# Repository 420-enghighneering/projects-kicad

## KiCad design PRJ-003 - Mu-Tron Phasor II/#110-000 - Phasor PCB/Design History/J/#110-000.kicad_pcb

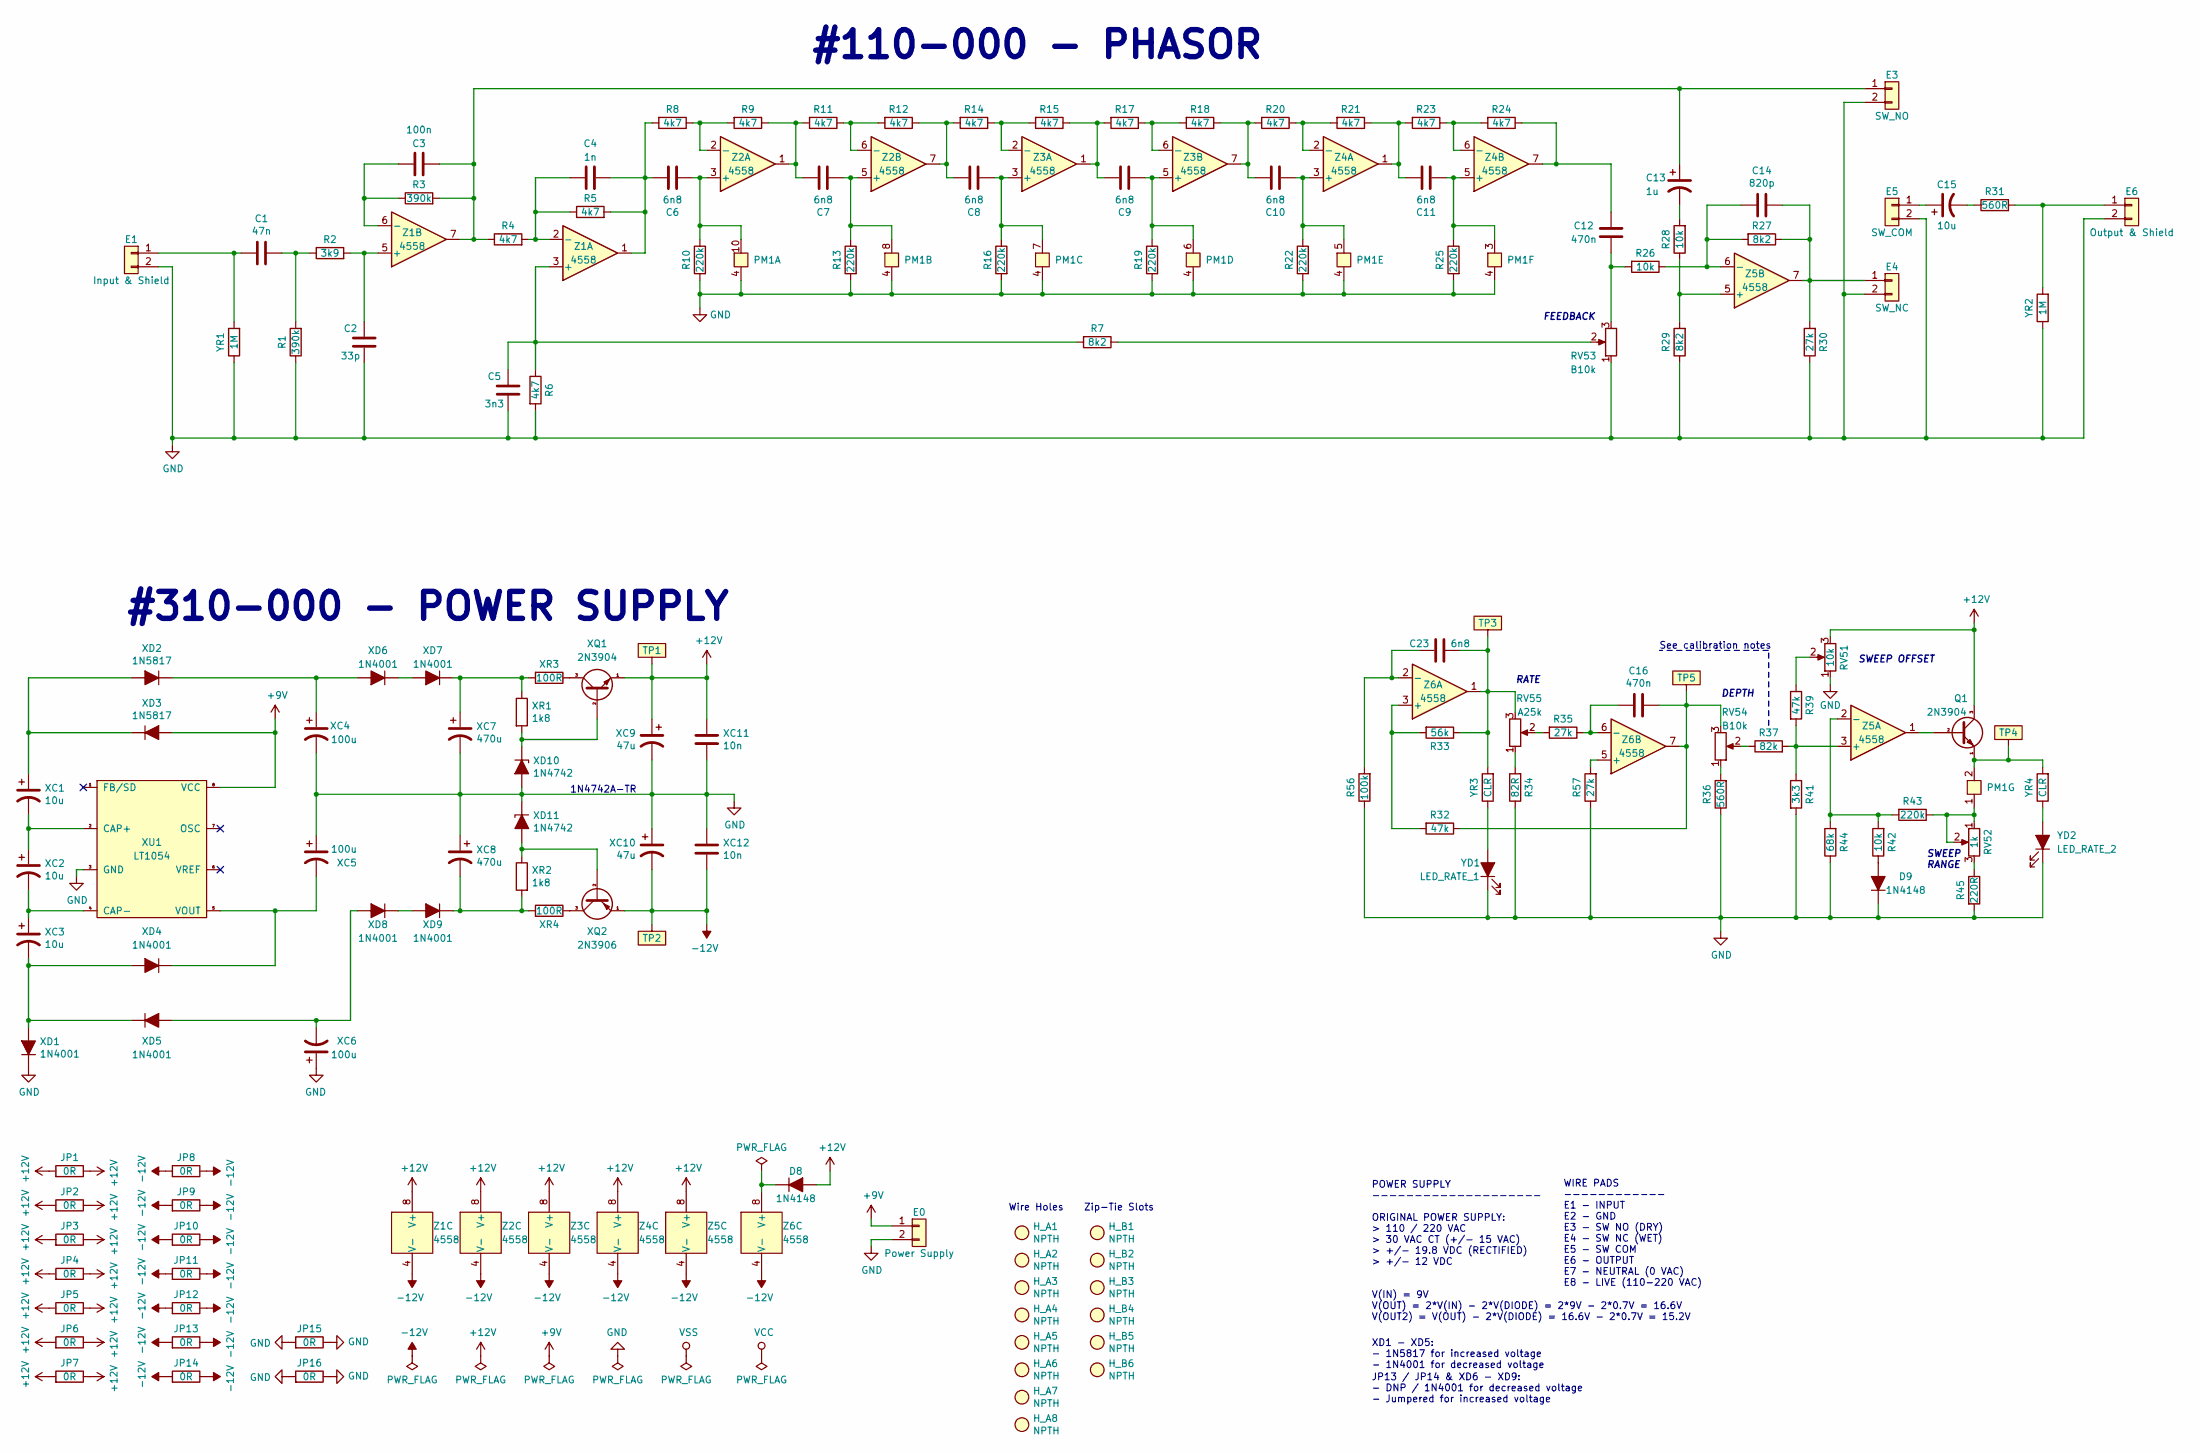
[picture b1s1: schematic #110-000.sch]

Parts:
C1: 47n; C_MKS2F024701C00KSSD
C2: 33p; C_FKP2O100331D00JSSD
C3: 100n; C_MKS2C031001A00KSSD
C4: 1n; C_FKS2G011001A00KSSD
C5: 3n3; C_FKS2G013301A00KSSD
C6, C7, C8, C9, C10, C11, C23: 6n8; C_FKS2G016801B00KSSD
C12, C16: 470n; C_MKS2C034701C00KSSD
C13: 1u; C_UMA1H010MDD
C14: 820p; C_FKP2J008201D00HSSD
C15: 10u; C_UMA1V100MDD
D8, D9: 1N4148; D_P10.16_DO35
E0: Power Supply; E_WIRE_PAD_2x
E1: Input & Shield; E_WIRE_PAD_2x
E3: SW_NO; E_WIRE_PAD_2x
E4: SW_NC; E_WIRE_PAD_2x
E5: SW_COM; E_WIRE_PAD_2x
E6: Output & Shield; E_WIRE_PAD_2x
H_A1, H_A2, H_A3, H_A4, H_A5, H_A6, H_A7, H_A8: NPTH; H_NPTH
H_B1, H_B2, H_B3, H_B4, H_B5, H_B6: NPTH; E_ZIPTIE_NPTH
JP1, JP2, JP3, JP4, JP5, JP6, JP7, JP8, JP9, JP10, JP11, JP12, JP13, JP14, JP15, JP16: 0R; R_0R_JUMPER_P10.16
PM1: Photomodule; PM_DIP-10
Q1: 2N3904; Q_P2.54
R1, R3: 390k; R_P10.16
R2: 3k9; R_P10.16
R4, R5, R6, R8, R9, R11, R12, R14, R15, R17, R18, R20, R21, R23, R24: 4k7; R_P10.16
R7, R27, R29: 8k2; R_P10.16
R10, R13, R16, R19, R22, R25, R43: 220k; R_P10.16
R26, R28, R42: 10k; R_P10.16
R30, R35, R57: 27k; R_P10.16
R31, R36: 560R; R_P10.16
R32, R39: 47k; R_P10.16
R33: 56k; R_P10.16
R34: 82R; R_P10.16
R37: 82k; R_P10.16
R41: 3k3; R_P10.16
R44: 68k; R_P10.16
R45: 220R; R_P10.16
R56: 100k; R_P10.16
RV51: 10k; R_TRIM
RV52: 1k; R_TRIM
RV53, RV54: B10k; R_POT
RV55: A25k; R_POT
TP1: TP1; TP_SMD_R_3mm
TP2: TP2; TP_SMD_R_3mm
TP3: TP3; TP_SMD_R_3mm
TP4: TP4; TP_SMD_R_3mm
TP5: TP5; TP_SMD_R_3mm
XC1, XC2, XC3: 10u; C_UMA1V100MDD
XC4, XC5, XC6: 100u; C_UMA1E101MDD
XC7, XC8: 470u; C_ANGLED
XC9, XC10: 47u; C_UMA1V470MDD
XC11, XC12: 10n; C_FKS2G021001C00KSSD
XD1, XD4, XD5, XD6, XD7, XD8, XD9: 1N4001; D_P10.16
XD2, XD3: 1N5817; D_P10.16
XD10, XD11: 1N4742; D_P10.16_DO35
XQ1: 2N3904; Q_P2.54
XQ2: 2N3906; Q_P2.54
XR1, XR2: 1k8; R_P10.16
XR3, XR4: 100R; R_P10.16
XU1: LT1054; U_DIP-8
YD1: LED_RATE_1; E_WIRE_PAD_2x
YD2: LED_RATE_2; E_WIRE_PAD_2x
YR1, YR2: 1M; R_P10.16
YR3, YR4: CLR; R_P10.16
Z1, Z2, Z3, Z4, Z5, Z6: 4558; U_DIP-8

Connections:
+9V: E0.1, XD3.1 (A), XU1.8 (VCC)
+12V: D8.1 (A), JP1.1, JP1.2, JP2.1, JP2.2, JP3.1, JP3.2, JP4.1, JP4.2, JP5.1, JP5.2, JP6.1, JP6.2, JP7.1, JP7.2, Q1.3 (C), RV51.3, TP1.1, XC9.1, XC11.1, XQ1.1 (E), Z1.8 (V+), Z2.8 (V+), Z3.8 (V+), Z4.8 (V+), Z5.8 (V+)
-12V: JP8.1, JP8.2, JP9.1, JP9.2, JP10.1, JP10.2, JP11.1, JP11.2, JP12.1, JP12.2, JP13.1, JP13.2, JP14.1, JP14.2, TP2.1, XC10.2, XC12.2, XQ2.1 (E), Z1.4 (V-), Z2.4 (V-), Z3.4 (V-), Z4.4 (V-), Z5.4 (V-), Z6.4 (V-)
GND: C2.2, C5.2, D9.2 (K), E0.2, E1.2, E3.2, E4.2, E5.2, E6.2, JP15.1, JP15.2, JP16.1, JP16.2, PM1.4, PM1.9, R1.1, R6.2, R10.2, R13.2, R16.2, R19.2, R22.2, R25.2, R29.1, R30.1, R34.1, R36.1, R41.2, R44.1, R45.2, R56.1, R57.1, RV51.1, RV53.1, XC4.2, XC5.1, XC6.1, XC7.2, XC8.1, XC9.2, XC10.1, XC11.2, XC12.1, XD1.2 (K), XD10.1 (A), XD11.2 (K), XU1.3 (GND), YD1.1 (K), YD2.1 (K), YR1.1, YR2.1
unnamed: C1.1, E1.1, YR1.2
unnamed: C1.2, R1.2, R2.1
unnamed: C2.1, R2.2, Z1.5 (+)
unnamed: C3.1, R3.1, Z1.6 (-)
unnamed: C4.1, R4.2, R5.1, Z1.2 (-)
unnamed: C4.2, C6.1, R5.2, R8.2, Z1.1
unnamed: C5.1, R6.1, R7.2, Z1.3 (+)
unnamed: C6.2, PM1.10, R10.1, Z2.3 (+)
unnamed: C7.1, R9.1, R11.2, Z2.1
unnamed: C7.2, PM1.8, R13.1, Z2.5 (+)
unnamed: C8.1, R12.1, R14.2, Z2.7
unnamed: C8.2, PM1.7, R16.1, Z3.3 (+)
unnamed: C9.1, R15.1, R17.2, Z3.1
unnamed: C9.2, PM1.6, R19.1, Z3.5 (+)
unnamed: C10.1, R18.1, R20.2, Z3.7
unnamed: C10.2, PM1.5, R22.1, Z4.3 (+)
unnamed: C11.1, R21.1, R23.2, Z4.1
unnamed: C11.2, PM1.3, R25.1, Z4.5 (+)
unnamed: C12.1, R24.1, Z4.7
unnamed: C12.2, R26.2, RV53.3
unnamed: C3.2, C13.1, E3.1, R3.2, R4.1, Z1.7
unnamed: C13.2, R28.2
unnamed: C14.1, R26.1, R27.2, Z5.6 (-)
unnamed: C14.2, E4.1, R27.1, R30.2, Z5.7
unnamed: C15.1, E5.1
unnamed: C15.2, R31.1
unnamed: C16.1, R35.1, Z6.6 (-)
unnamed: C16.2, R32.1, RV54.3, TP5.1, Z6.7
unnamed: C23.1, R56.2, Z6.2 (-)
unnamed: C23.2, R33.1, RV55.3, TP3.1, YR3.2, Z6.1
unnamed: D8.2 (K), Z6.8 (V+)
unnamed: D9.1 (A), R42.1
unnamed: E6.1, R31.2, YR2.2
unnamed: PM1.1, R43.1, RV52.1, RV52.2
unnamed: PM1.2, Q1.1 (E), TP4.1, YR4.2
unnamed: Q1.2 (B), Z5.1
unnamed: R7.1, RV53.2
unnamed: R8.1, R9.2, Z2.2 (-)
unnamed: R11.1, R12.2, Z2.6 (-)
unnamed: R14.1, R15.2, Z3.2 (-)
unnamed: R17.1, R18.2, Z3.6 (-)
unnamed: R20.1, R21.2, Z4.2 (-)
unnamed: R23.1, R24.2, Z4.6 (-)
unnamed: R28.1, R29.2, Z5.5 (+)
unnamed: R32.2, R33.2, Z6.3 (+)
unnamed: R34.2, RV55.1
unnamed: R35.2, RV55.2
unnamed: R36.2, RV54.1
unnamed: R37.1, RV54.2
unnamed: R37.2, R39.2, R41.1, Z5.3 (+)
unnamed: R39.1, RV51.2
unnamed: R42.2, R43.2, R44.2, Z5.2 (-)
unnamed: R45.1, RV52.3
unnamed: R57.2, Z6.5 (+)
unnamed: XC1.1, XD2.1 (A), XD3.2 (K)
unnamed: XC1.2, XC2.1, XU1.2 (CAP+)
unnamed: XC2.2, XC3.1, XU1.4 (CAP-)
unnamed: XC3.2, XD1.1 (A), XD4.1 (A), XD5.2 (K)
unnamed: XC4.1, XD2.2 (K), XD6.1 (A)
unnamed: XC5.2, XD4.2 (K), XU1.5 (VOUT)
unnamed: XC6.2, XD5.1 (A), XD8.1 (A)
unnamed: XC7.1, XD7.2 (K), XR1.1, XR3.2
unnamed: XC8.2, XD9.2 (K), XR2.2, XR4.2
unnamed: XD6.2 (K), XD7.1 (A)
unnamed: XD8.2 (K), XD9.1 (A)
unnamed: XD10.2 (K), XQ1.2 (B), XR1.2
unnamed: XD11.1 (A), XQ2.2 (B), XR2.1
unnamed: XQ1.3 (C), XR3.1
unnamed: XQ2.3 (C), XR4.1
unnamed: YD1.2 (A), YR3.1
unnamed: YD2.2 (A), YR4.1

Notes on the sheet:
1N4742A-TR
POWER SUPPLY -------------------- ORIGINAL POWER SUPPLY: > 110 / 220 VAC > 30 VAC CT (+/- 15 VAC) > +/- 19.8 VDC (RECTIFIED) > +/- 12 VDC V(IN) = 9V V(OUT) = 2*V(IN) - 2*V(DIODE) = 2*9V - 2*0.7V = 16.6V V(OUT2) = V(OUT) - 2*V(DIODE) = 16.6V - 2*0.7V = 15.2V
SWEEP OFFSET
SWEEP RANGE
DEPTH
RATE
FEEDBACK
WIRE PADS ------------ E1 - INPUT E2 - GND E3 - SW NO (DRY) E4 - SW NC (WET) E5 - SW COM E6 - OUTPUT E7 - NEUTRAL (0 VAC) E8 - LIVE (110-220 VAC)
XD1 - XD5: - 1N5817 for increased voltage - 1N4001 for decreased voltage
JP13 / JP14 & XD6 - XD9: - DNP / 1N4001 for decreased voltage - Jumpered for increased voltage
#310-000 - POWER SUPPLY
#110-000 - PHASOR
See calibration notes
Zip-Tie Slots
Wire Holes

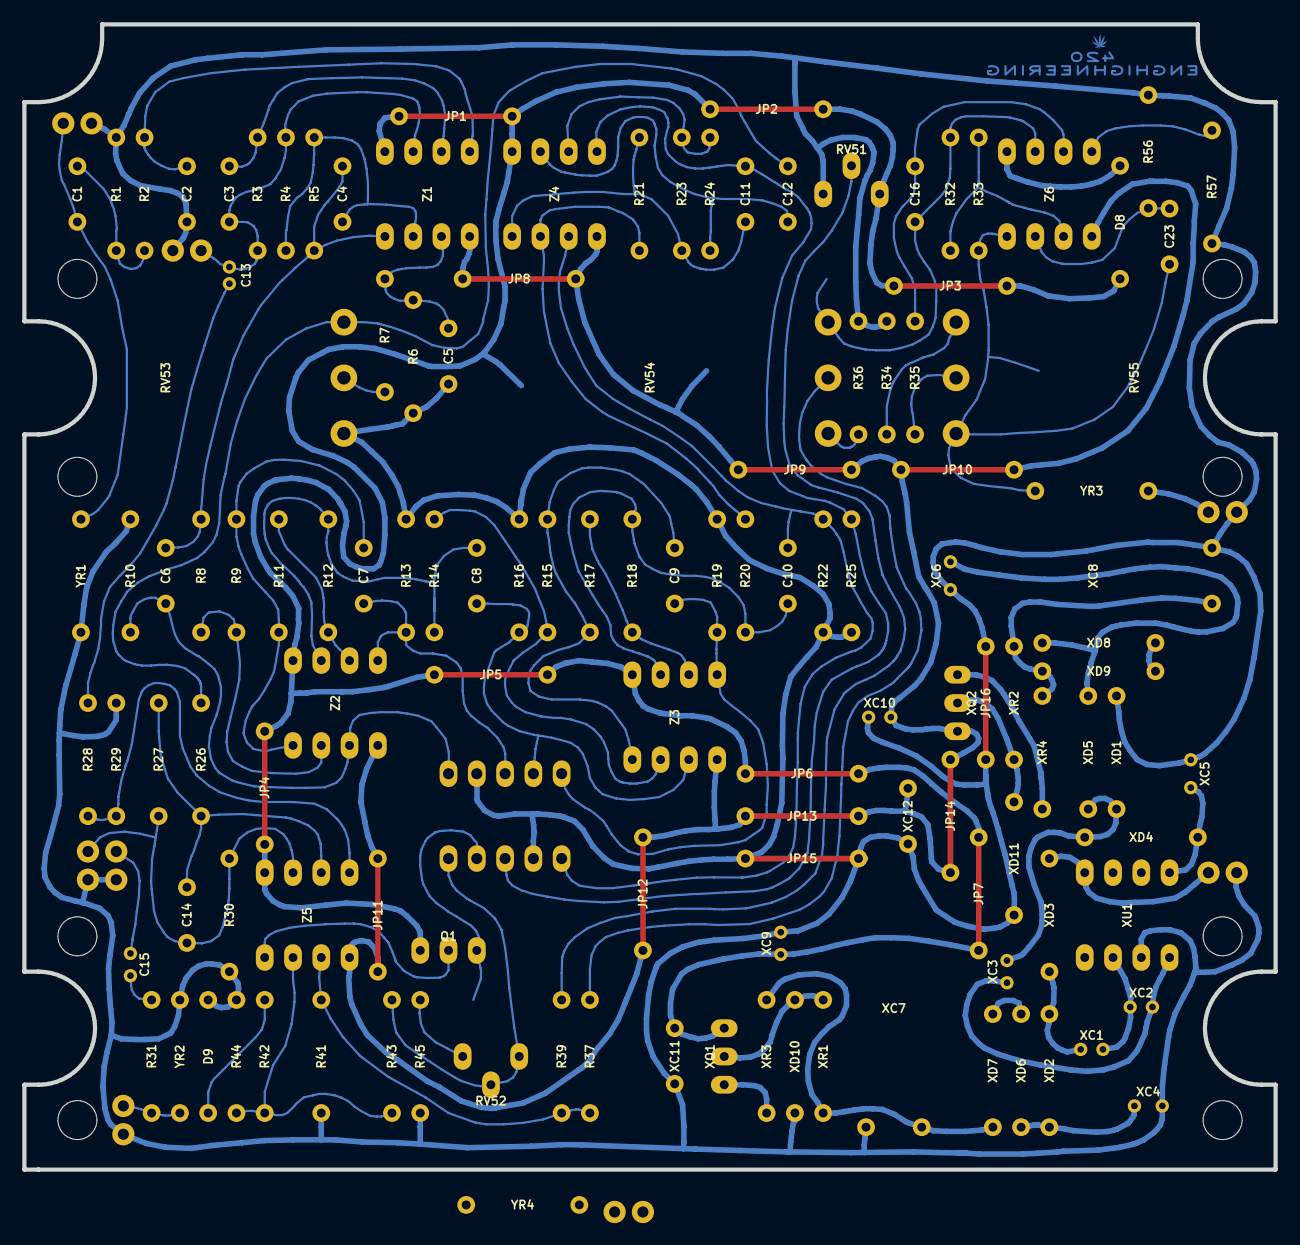
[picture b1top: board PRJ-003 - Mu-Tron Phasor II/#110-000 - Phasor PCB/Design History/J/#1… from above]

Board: 2 copper layers, 112.4 x 102.9 mm, 154 parts (0 on the bottom side), 75 nets.

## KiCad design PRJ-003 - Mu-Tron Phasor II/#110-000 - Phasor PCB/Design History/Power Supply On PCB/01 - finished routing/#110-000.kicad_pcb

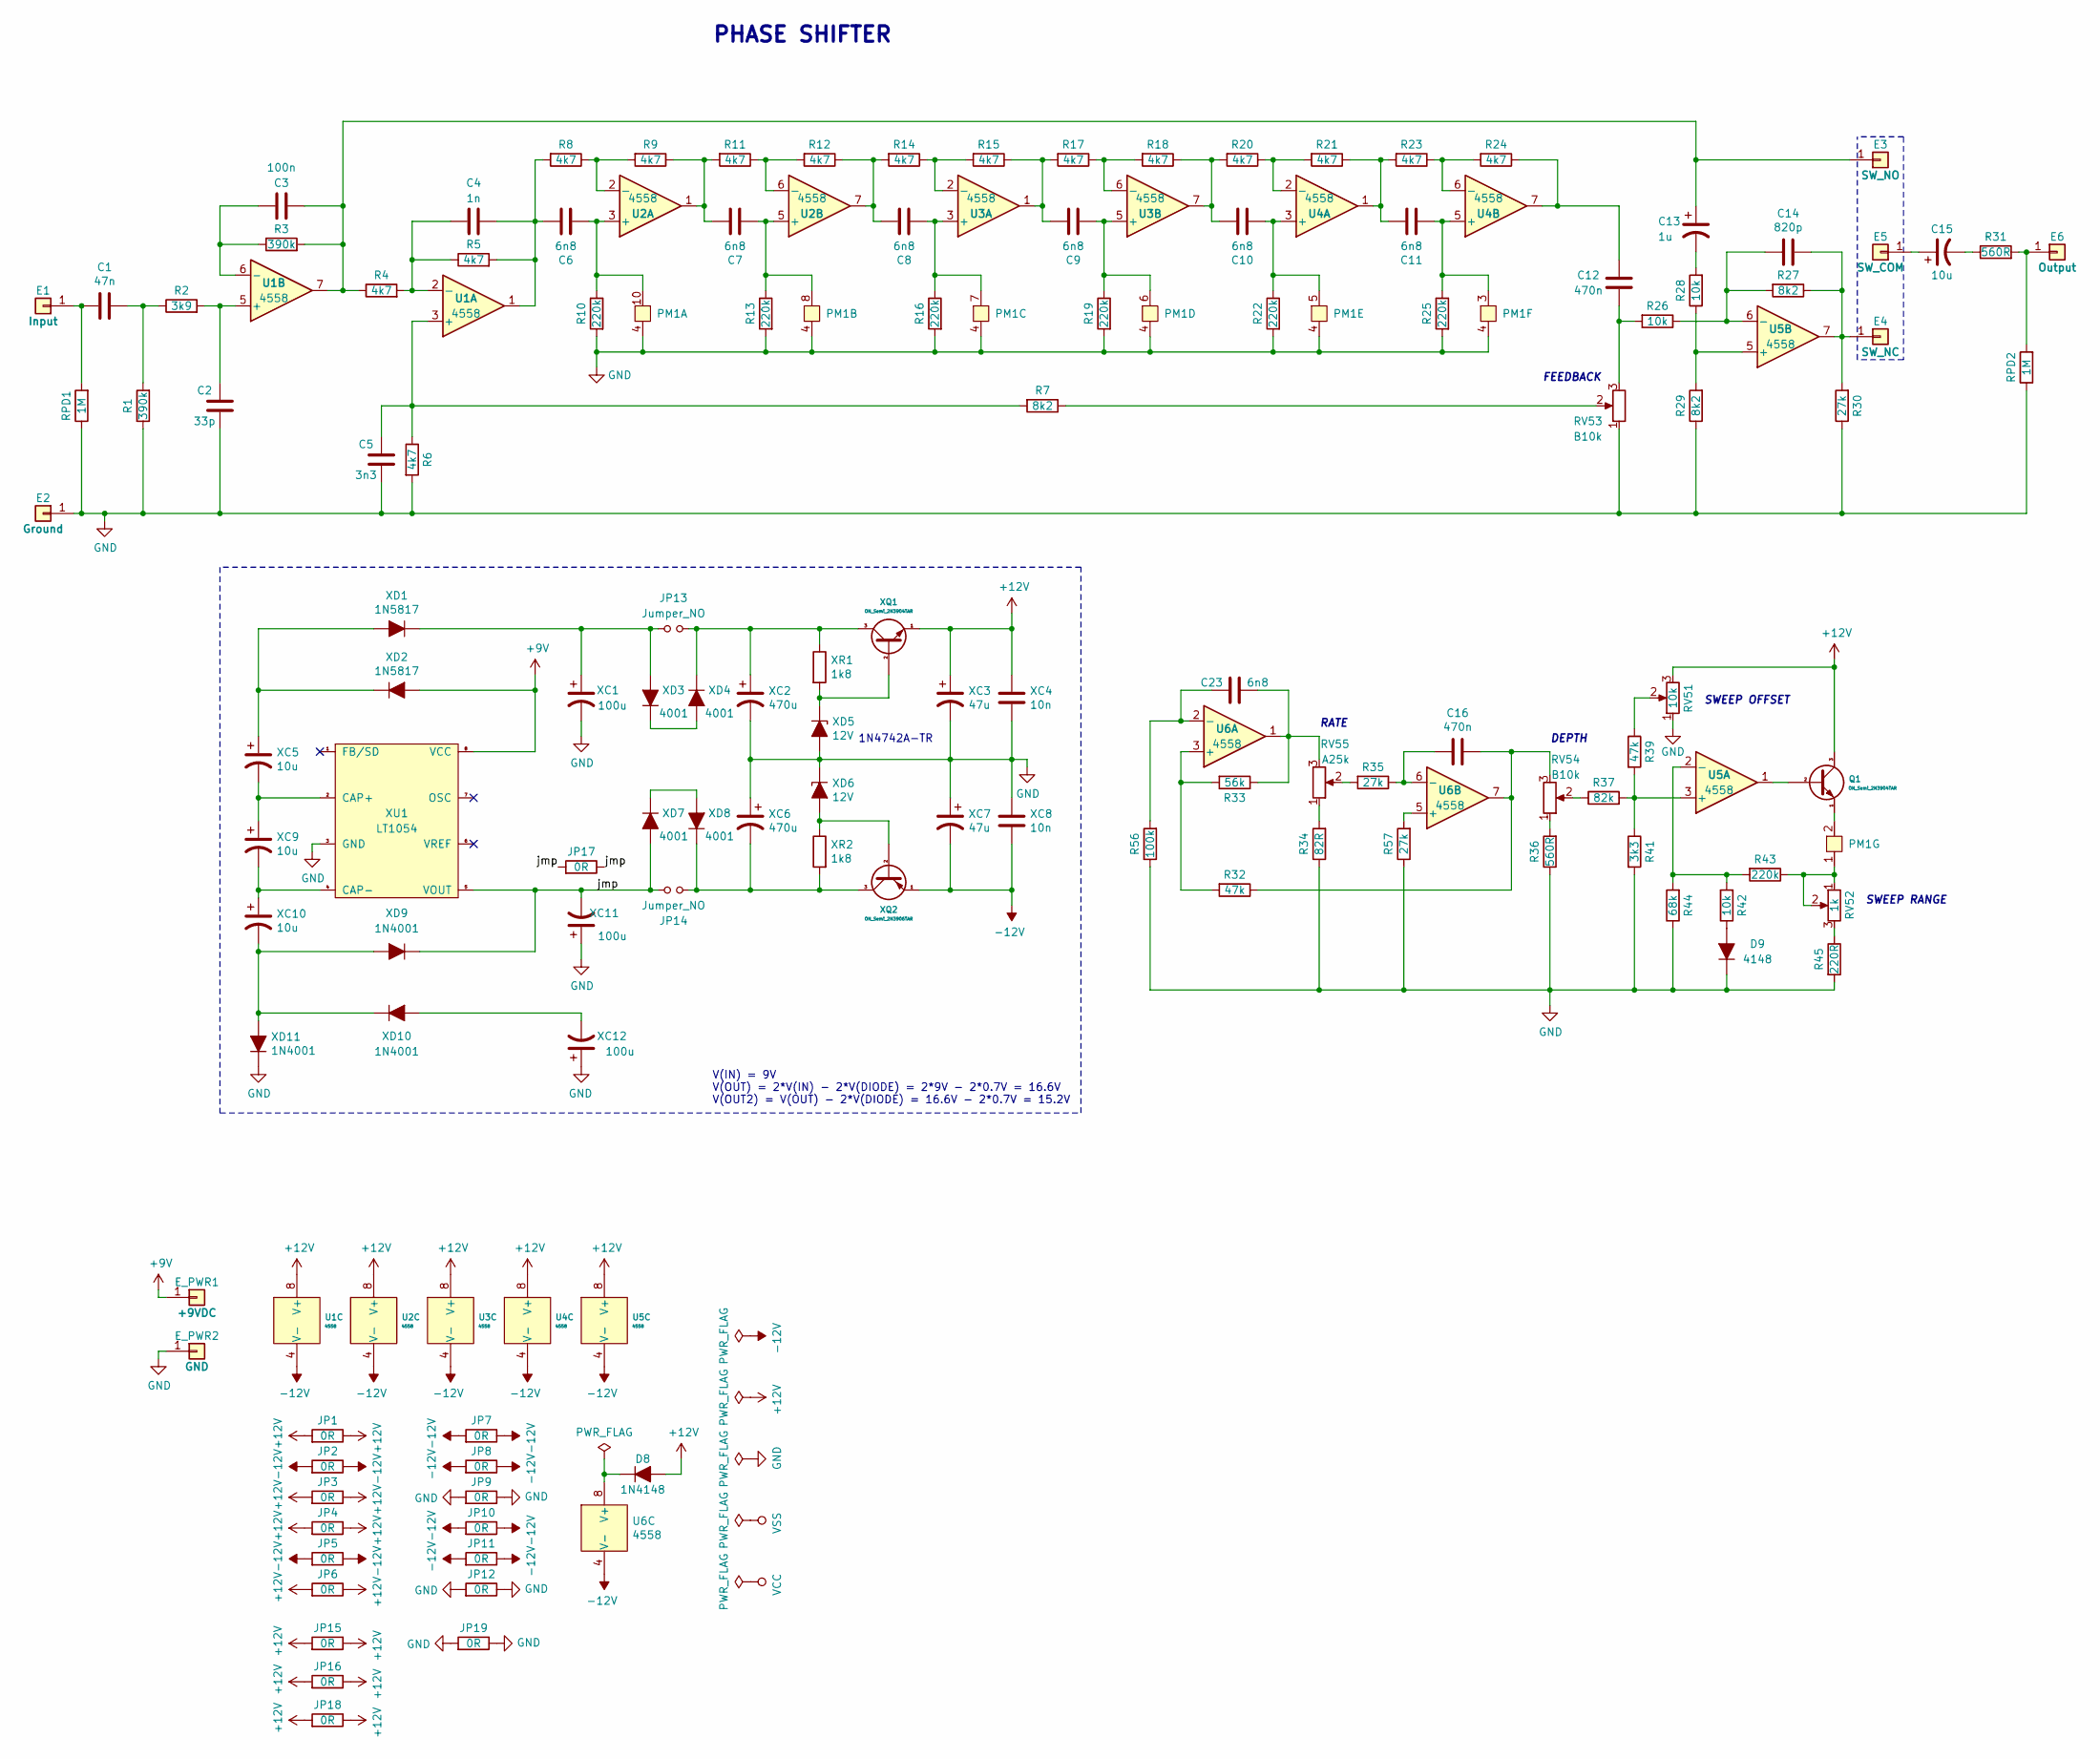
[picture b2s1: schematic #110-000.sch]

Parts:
C1: 47n; Wima_MKS2F024701C00KSSD
C2: 33p; Wima_FKP2J001001D00JSSD
C3: 100n; Wima_MKS2F031001E00KSSD
C4: 1n; Wima_FKS2G011001A00KSSD
C5: 3n3; Wima_FKS2G013301A00KSSD
C6, C7, C8, C9, C10, C11, C23: 6n8; Wima_FKS2G016801B00KSSD
C12, C16: 470n; Wima_MKS2C034701C00KSSD
C13: 1u; 1.0uF_50V_4x5x1.5_UMA1H010MDD
C14: 820p; Wima_FKP2J006801D00JSSD
C15: 10u; 10uF_35V_5x5x2_UMA1V100MDD
D8: 1N4148; DO-35_P10.16
D9: 4148; DO-35_P10.16
E1: Input; Wire_Pad_1x01
E2: Ground; Wire_Pad_1x01
E3: SW_NO; Wire_Pad_1x01
E4: SW_NC; Wire_Pad_1x01
E5: SW_COM; Wire_Pad_1x01
E6: Output; Wire_Pad_1x01
E_PWR1: +9VDC; Wire_Pad_1x01
E_PWR2: GND; Wire_Pad_1x01
JP1, JP2, JP3, JP4, JP5, JP6, JP7, JP8, JP9, JP10, JP11, JP12, JP15, JP16, JP17, JP18, JP19: 0R; R_0R_Wire_Jumper_P10.16
JP13, JP14: Jumper_NO; R_0R_Wire_Jumper_P10.16
PM1: Photomodule
Q1: ON_Semi_2N3904TAR
R1, R3: 390k; R_CC25_P10.16_H_390k
R2: 3k9; R_CC25_P10.16_H_3.9k
R4, R5, R6, R8, R9, R11, R12, R14, R15, R17, R18, R20, R21, R23, R24: 4k7; R_CC25_P10.16_H_4.7k
R7, R27, R29: 8k2; R_CC25_P10.16_H_8.2k
R10, R13, R16, R19, R22, R25, R43: 220k; R_CC25_P10.16_H_220k
R26, R28, R42: 10k; R_CC25_P10.16_H_10k
R30, R35, R57: 27k; R_CC25_P10.16_H_27k
R31, R36: 560R; R_CC25_P10.16_H_560R
R32, R39: 47k; R_CC25_P10.16_H_47k
R33: 56k; R_CC25_P10.16_H_56k
R34: 82R; R_CC25_P10.16_H_82R
R37: 82k; R_CC25_P10.16_H_82k
R41: 3k3; R_CC25_P10.16_H_3.3k
R44: 68k; R_CC25_P10.16_H_68k
R45: 220R; R_CC25_P10.16_H_220R
R56: 100k; R_CC25_P10.16_H_100k
RPD1, RPD2: 1M; R_CC25_P10.16_H_1.0M
RV51: 10k; Bourns_3362P-1-104
RV52: 1k; Bourns_3362P-1-104
RV53, RV54: B10k; Alpha_Taiwan_RV16AF-41
RV55: A25k; Alpha_Taiwan_RV16AF-41
U1, U2, U3, U4, U5, U6: 4558; Texas_Instruments_RC4558P
XC1, XC11, XC12: 100u; 100uF_25V_8x5x2.5_UMA1E101MDD
XC2, XC6: 470u; Electrolytic_Radial_Angled_D10.0_H17.0_P5.0
XC3, XC7: 47u; 47uF_35V_8x5x2.5_UMA1V470MDD
XC4, XC8: 10n; Wima_FKS2G021001C00KSSD
XC5, XC9, XC10: 10u; 10uF_35V_5x5x2_UMA1V100MDD
XD1, XD2: 1N5817; DO-41_P10.16
XD3, XD4, XD7, XD8: 4001; DO-41_P10.16
XD5, XD6: 12V; DO-41_P10.16
XD9, XD10, XD11: 1N4001; DO-41_P10.16
XQ1: ON_Semi_2N3904TAR
XQ2: ON_Semi_2N3906TAR
XR1, XR2: 1k8; R_CC25_P10.16_H_1.8k
XU1: LT1054

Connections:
+9V: E_PWR1.1, XD2.1 (A), XU1.8 (VCC)
+12V: D8.1 (A), JP1.1, JP1.2, JP3.1, JP3.2, JP4.1, JP4.2, JP6.1, JP6.2, JP15.1, JP15.2, JP16.1, JP16.2, JP18.1, JP18.2, Q1.3 (C), RV51.3, U1.8 (V+), U2.8 (V+), U3.8 (V+), U4.8 (V+), U5.8 (V+), XC3.1, XC4.1, XQ1.1 (E)
-12V: JP2.1, JP2.2, JP5.1, JP5.2, JP7.1, JP7.2, JP8.1, JP8.2, JP10.1, JP10.2, JP11.1, JP11.2, U1.4 (V-), U2.4 (V-), U3.4 (V-), U4.4 (V-), U5.4 (V-), U6.4 (V-), XC7.2, XC8.2, XQ2.1 (E)
/jmp: JP14.1, JP17.1, JP17.2, XC11.2, XD7.1 (A), XD9.2 (K), XU1.5 (VOUT)
GND: C2.2, C5.2, D9.2 (K), E2.1, E_PWR2.1, JP9.1, JP9.2, JP12.1, JP12.2, JP19.1, JP19.2, PM1.4, PM1.9, R1.1, R6.2, R10.2, R13.2, R16.2, R19.2, R22.2, R25.2, R29.1, R30.1, R34.1, R36.1, R41.2, R44.1, R45.2, R56.1, R57.1, RPD1.1, RPD2.1, RV51.1, RV53.1, XC1.2, XC2.2, XC3.2, XC4.2, XC6.1, XC7.1, XC8.1, XC11.1, XC12.1, XD5.1 (A), XD6.2 (K), XD11.2 (K), XU1.3 (GND)
unnamed: C1.1, E1.1, RPD1.2
unnamed: C1.2, R1.2, R2.1
unnamed: C2.1, R2.2, U1.5 (+)
unnamed: C3.1, R3.1, U1.6 (-)
unnamed: C4.1, R4.2, R5.1, U1.2 (-)
unnamed: C4.2, C6.1, R5.2, R8.2, U1.1
unnamed: C5.1, R6.1, R7.2, U1.3 (+)
unnamed: C6.2, PM1.10, R10.1, U2.3 (+)
unnamed: C7.1, R9.1, R11.2, U2.1
unnamed: C7.2, PM1.8, R13.1, U2.5 (+)
unnamed: C8.1, R12.1, R14.2, U2.7
unnamed: C8.2, PM1.7, R16.1, U3.3 (+)
unnamed: C9.1, R15.1, R17.2, U3.1
unnamed: C9.2, PM1.6, R19.1, U3.5 (+)
unnamed: C10.1, R18.1, R20.2, U3.7
unnamed: C10.2, PM1.5, R22.1, U4.3 (+)
unnamed: C11.1, R21.1, R23.2, U4.1
unnamed: C11.2, PM1.3, R25.1, U4.5 (+)
unnamed: C12.1, R24.1, U4.7
unnamed: C12.2, R26.2, RV53.3
unnamed: C3.2, C13.1, E3.1, R3.2, R4.1, U1.7
unnamed: C13.2, R28.2
unnamed: C14.1, R26.1, R27.2, U5.6 (-)
unnamed: C14.2, E4.1, R27.1, R30.2, U5.7
unnamed: C15.1, E5.1
unnamed: C15.2, R31.1
unnamed: C16.1, R35.1, U6.6 (-)
unnamed: C16.2, R32.1, RV54.3, U6.7
unnamed: C23.1, R56.2, U6.2 (-)
unnamed: C23.2, R33.1, RV55.3, U6.1
unnamed: D8.2 (K), U6.8 (V+)
unnamed: D9.1 (A), R42.1
unnamed: E6.1, R31.2, RPD2.2
unnamed: JP13.1, XC1.1, XD1.2 (K), XD3.1 (A)
unnamed: JP13.2, XC2.1, XD4.2 (K), XQ1.3 (C), XR1.1
unnamed: JP14.2, XC6.2, XD8.2 (K), XQ2.3 (C), XR2.2
unnamed: PM1.1, R43.1, RV52.1, RV52.2
unnamed: PM1.2, Q1.1 (E)
unnamed: Q1.2 (B), U5.1
unnamed: R7.1, RV53.2
unnamed: R8.1, R9.2, U2.2 (-)
unnamed: R11.1, R12.2, U2.6 (-)
unnamed: R14.1, R15.2, U3.2 (-)
unnamed: R17.1, R18.2, U3.6 (-)
unnamed: R20.1, R21.2, U4.2 (-)
unnamed: R23.1, R24.2, U4.6 (-)
unnamed: R28.1, R29.2, U5.5 (+)
unnamed: R32.2, R33.2, U6.3 (+)
unnamed: R34.2, RV55.1
unnamed: R35.2, RV55.2
unnamed: R36.2, RV54.1
unnamed: R37.1, RV54.2
unnamed: R37.2, R39.2, R41.1, U5.3 (+)
unnamed: R39.1, RV51.2
unnamed: R42.2, R43.2, R44.2, U5.2 (-)
unnamed: R45.1, RV52.3
unnamed: R57.2, U6.5 (+)
unnamed: XC5.1, XD1.1 (A), XD2.2 (K)
unnamed: XC5.2, XC9.1, XU1.2 (CAP+)
unnamed: XC9.2, XC10.1, XU1.4 (CAP-)
unnamed: XC10.2, XD9.1 (A), XD10.2 (K), XD11.1 (A)
unnamed: XC12.2, XD10.1 (A)
unnamed: XD3.2 (K), XD4.1 (A)
unnamed: XD5.2 (K), XQ1.2 (B), XR1.2
unnamed: XD6.1 (A), XQ2.2 (B), XR2.1
unnamed: XD7.2 (K), XD8.1 (A)

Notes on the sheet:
1N4742A-TR
V(IN) = 9V V(OUT) = 2*V(IN) - 2*V(DIODE) = 2*9V - 2*0.7V = 16.6V V(OUT2) = V(OUT) - 2*V(DIODE) = 16.6V - 2*0.7V = 15.2V
PHASE SHIFTER
SWEEP OFFSET
SWEEP RANGE
DEPTH
RATE
FEEDBACK

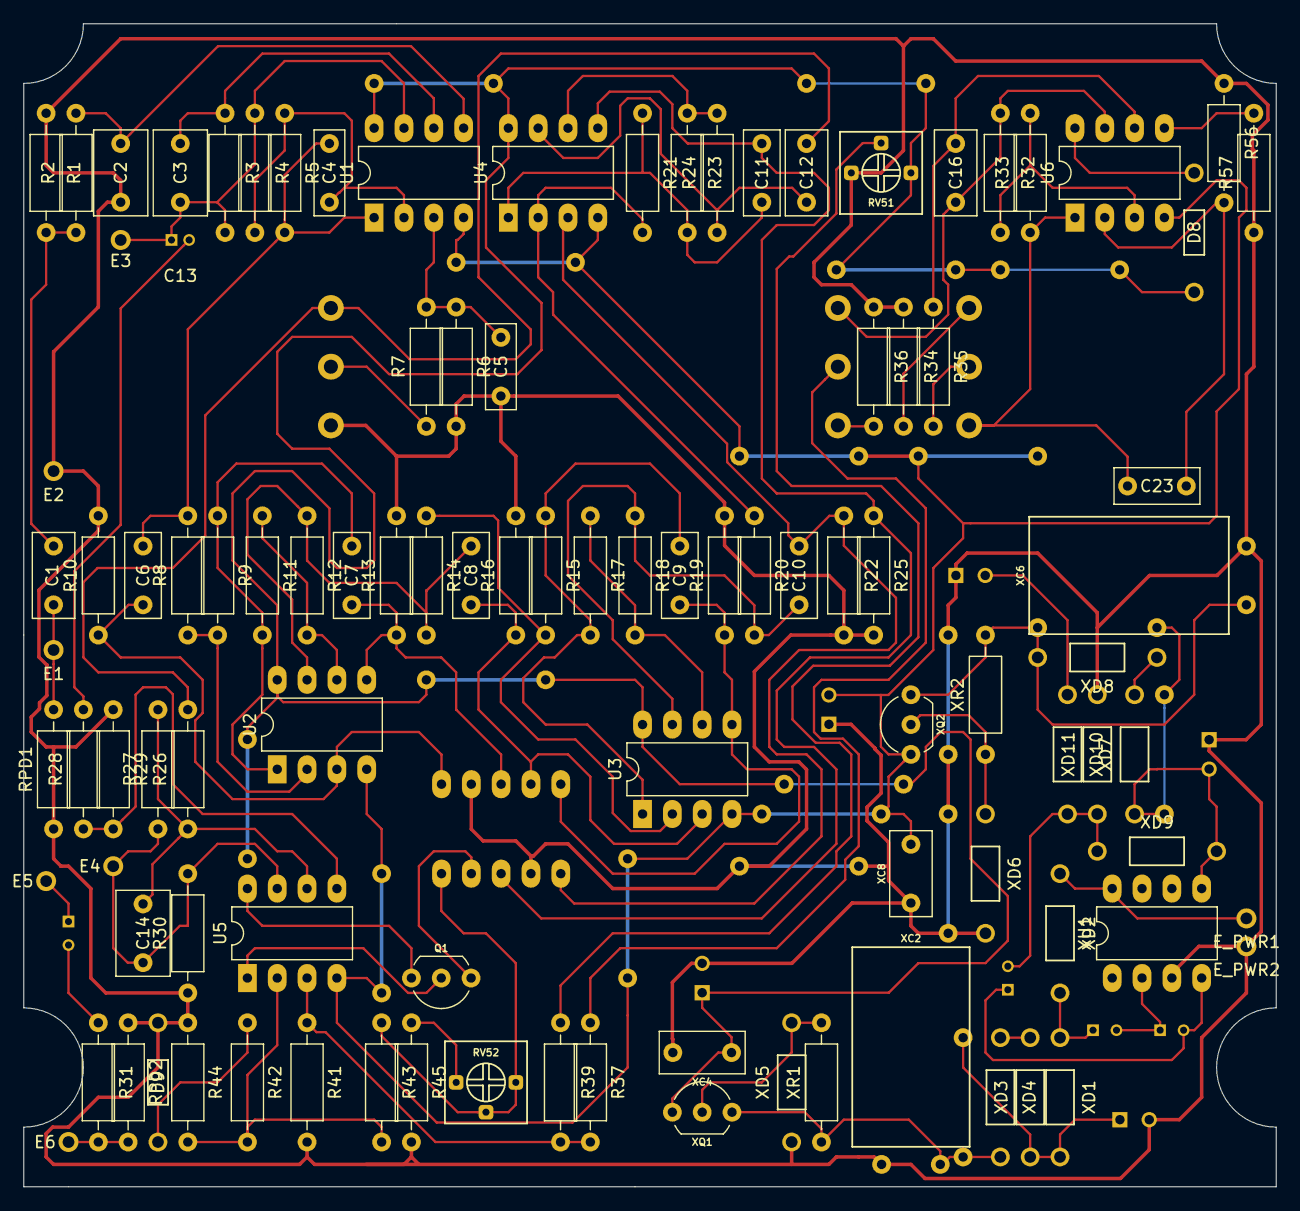
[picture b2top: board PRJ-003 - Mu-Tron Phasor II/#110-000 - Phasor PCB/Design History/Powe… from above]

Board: 2 copper layers, 106.7 x 99.1 mm, 134 parts (0 on the bottom side), 71 nets.
